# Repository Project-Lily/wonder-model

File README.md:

<div style="text-align: center">
<h1>Wonder Reader</h1>

<p>Repository for circuit, and 3D CAD models<p>
</div>

### Circuit

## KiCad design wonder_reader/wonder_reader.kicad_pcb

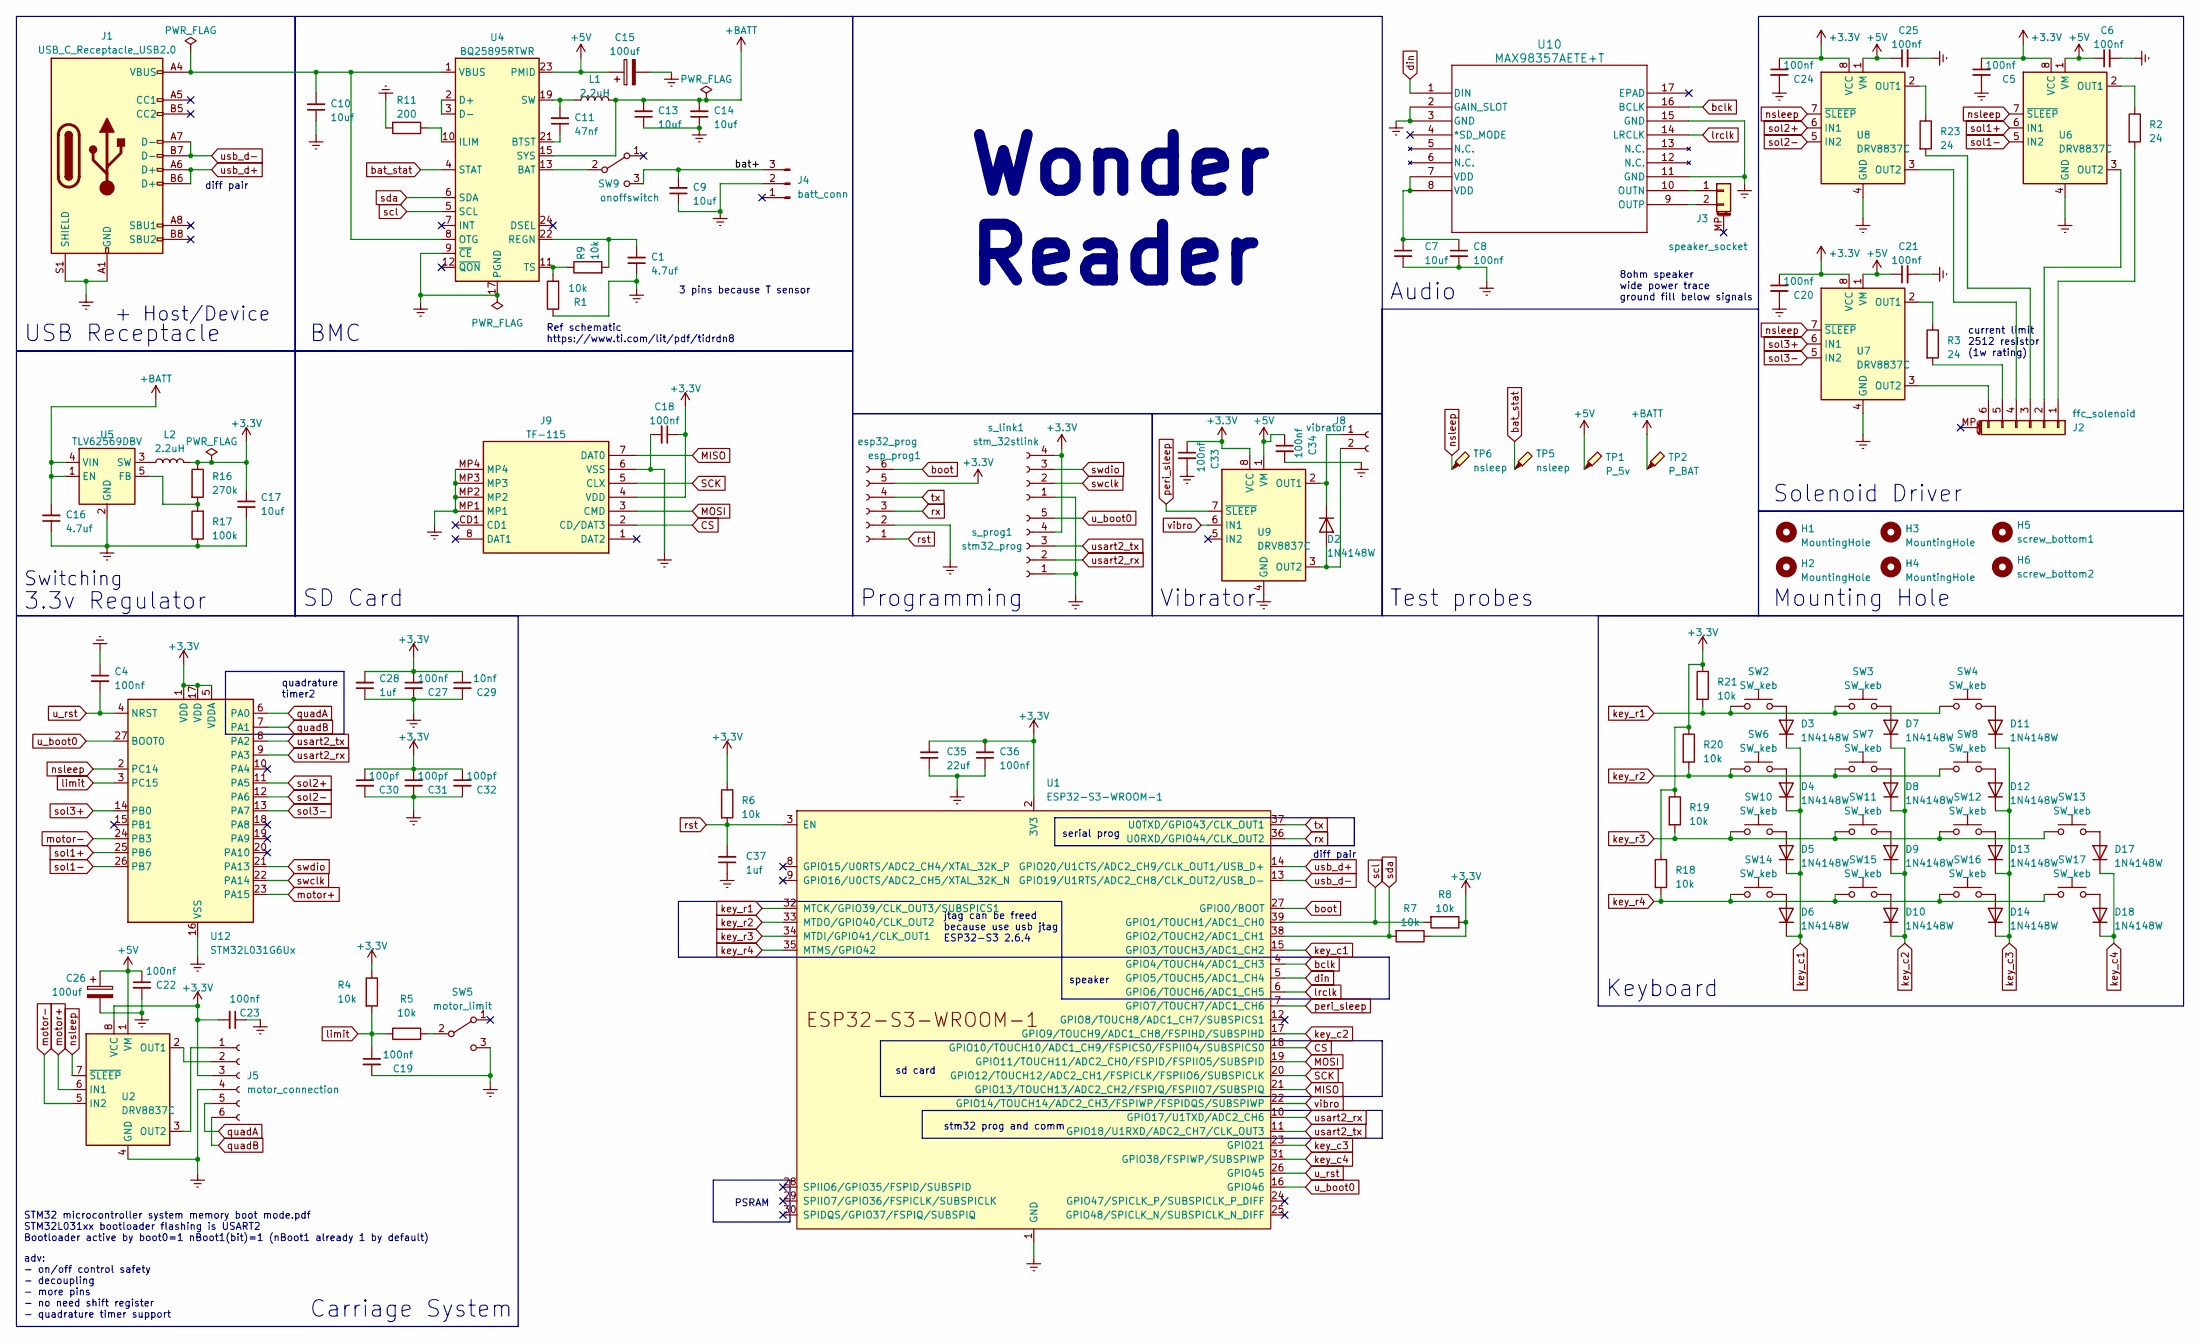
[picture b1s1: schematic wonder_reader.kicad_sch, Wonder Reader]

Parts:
C1, C16: 4.7uf; C_0805_2012Metric; LCSC Part C1779
C4, C5, C6, C8, C18, C19, C20, C21, C22, C23, C24, C25, C27, C33, C34, C36: 100nf; C_0402_1005Metric; LCSC Part C1525
C7, C9, C10, C13, C14, C17: 10uf; C_0805_2012Metric; LCSC Part C15850
C11: 47nf; C_0603_1608Metric; LCSC Part C1622
C15, C26: 100uf; CP_Elec_6.3x5.4; LCSC Part C1622
C28, C37: 1uf; C_0402_1005Metric; LCSC Part C52923
C29: 10nf; C_0402_1005Metric; LCSC Part C15195
C30, C31, C32: 100pf; C_0402_1005Metric; LCSC Part C1546
C35: 22uf; C_0805_2012Metric; LCSC Part C45783
D2, D3, D4, D5, D6, D7, D8, D9, D10, D11, D12, D13, D14, D17, D18: 1N4148W; D_SOD-123; LCSC Part C81598
H1, H2, H3, H4: MountingHole; MountingHole_2.2mm_M2
H5: screw_bottom1; MountingHole_5.3mm_M5
H6: screw_bottom2; MountingHole_5.3mm_M5
J1: USB_C_Receptacle_USB2.0; USB_C_Receptacle_G-Switch_GT-USB-7010ASV; LCSC Part C2765186
J2: ffc_solenoid; Hirose_FH12-6S-0.5SH_1x06-1MP_P0.50mm_Horizontal; LCSC Part C2856796
J3: speaker_socket; JST_GH_BM02B-GHS-TBT_1x02-1MP_P1.25mm_Vertical; LCSC Part C161690
J4: batt_conn; JST_PH_S3B-PH-K_1x03_P2.00mm_Horizontal; LCSC Part C157929
J5: motor_connection; PinHeader_1x06_P1.27mm_Vertical
J8: vibrator; PinHeader_1x02_P1.27mm_Vertical
J9: TF-115; TF115; Manufacturer_Part_Number TF-115; LCSC Part C266620
L1, L2: 2.2uH; L_1210_3225Metric; LCSC Part C295335
R1, R4, R5, R6, R7, R8, R9, R18, R19, R20, R21: 10k; R_0603_1608Metric; LCSC Part C25804
R2, R3, R23: 24; R_2512_6332Metric
R11: 200; R_0603_1608Metric; LCSC Part C8218
R16: 270k; R_0603_1608Metric; LCSC Part C103491
R17: 100k; R_0603_1608Metric; LCSC Part C25803
SW2, SW3, SW4, SW6, SW7, SW8, SW10, SW11, SW12, SW13, SW14, SW15, SW16, SW17: SW_keb; SW_Kailh_Choc_V1
SW5: motor_limit; SW_XKB_DM1-16UC-1; LCSC Part C466019
SW9: onoffswitch; G-Switch MK-12C02-G025; LCSC Part C963206
TP1: P_5v; TestPoint_Pad_1.0x1.0mm
TP2: P_BAT; TestPoint_Pad_1.0x1.0mm
TP5, TP6: nsleep; TestPoint_Pad_1.0x1.0mm
U1: ESP32-S3-WROOM-1; LCSC Part C2913197
U2, U6, U7, U8, U9: DRV8837C; WSON-8-1EP_2x2mm_P0.5mm_EP0.9x1.6mm; LCSC Part C191000
U4: BQ25895RTWR; Texas_S-PWQFN-N24_EP2.7x2.7mm_ThermalVias; LCSC Part C80200
U5: TLV62569DBV; SOT-23-5; LCSC Part C141836
U10: MAX98357AETE+T; 21-0136I_T1633-4_MXM; LCSC Part C910544
U12: STM32L031G6Ux; QFN-28_4x4mm_P0.5mm; LCSC Part C96514
esp_prog1: esp32_prog; PinHeader_1x06_P2.00mm_Vertical
s_link1: stm_32stlink; PinHeader_1x04_P2.00mm_Vertical
s_prog1: stm32_prog; PinHeader_1x05_P2.00mm_Vertical

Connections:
+3.3V: C5.1, C17.1, C18.1, C20.1, C23.2, C24.1, C27.1, C28.2, C29.1, C30.1, C31.1, C32.1, C33.1, C35.2, C36.2, J5.3, J9.4 (VDD), L2.2, R4.1, R6.1, R7.1, R8.1, R16.1, R18.1, R19.1, R20.1, R21.1, U1.2 (3V3), U2.8 (VCC), U6.8 (VCC), U7.8 (VCC), U8.8 (VCC), U9.8 (VCC), U12.1 (VDD), U12.5 (VDDA), U12.17 (VDD), esp_prog1.5, s_link1.4, s_prog1.4
+5V: C6.1, C15.1, C21.1, C22.1, C25.1, C26.1, C34.1, TP1.1, U2.1 (VM), U4.23 (PMID), U6.1 (VM), U7.1 (VM), U8.1 (VM), U9.1 (VM)
+BATT: C13.2, C14.2, C16.2, L1.2, TP2.1, U4.15 (SYS), U4.16 (SYS), U5.1 (EN), U5.4 (VIN)
/bat+: C9.2, J4.3, SW9.3 (C)
CS: J9.2 (CD/DAT3), U1.18 (GPIO10/TOUCH10/ADC1_CH9/FSPICS0/FSPIIO4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)
Earth: C1.1, C4.1, C5.2, C6.2, C7.2, C8.2, C9.1, C10.1, C13.1, C14.1, C15.2, C16.1, C17.2, C18.2, C19.2, C20.2, C21.2, C22.2, C23.1, C24.2, C25.2, C26.2, C27.2, C28.1, C29.2, C30.2, C31.2, C32.2, C33.2, C34.2, C35.1, C36.1, C37.1, J1.A1 (GND), J1.A12 (GND), J1.B1 (GND), J1.B12 (GND), J1.S1 (SHIELD), J4.2, J5.4, J9.6 (VSS), J9.MP1, J9.MP2, J9.MP3, J9.MP4, R1.1, R11.2, R17.1, SW5.3 (C), U1.1 (GND), U1.40 (GND), U1.41 (GND), U2.4 (GND), U2.9 (GND), U4.9 (~CE), U4.17 (PGND), U4.18 (PGND), U4.25 (PGND), U5.2 (GND), U6.4 (GND), U6.9 (GND), U7.4 (GND), U7.9 (GND), U8.4 (GND), U8.9 (GND), U9.4 (GND), U9.9 (GND), U10.2 (GAIN_SLOT), U10.3 (GND), U10.11 (GND), U10.15 (GND), U12.16 (VSS), U12.28 (VSS), esp_prog1.2, s_link1.1, s_prog1.1
MISO: J9.7 (DAT0), U1.21 (GPIO13/TOUCH13/ADC2_CH2/FSPIQ/FSPIIO7/S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)
MOSI: J9.3 (CMD), U1.19 (GPIO11/TOUCH11/ADC2_CH0/FSPID/FSPIIO5/S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)
unnamed: C7.1, C8.1, U10.7 (VDD), U10.8 (VDD)
unnamed: C11.2, L1.1, U4.19 (SW), U4.20 (SW)
unnamed: D2.2 (A), J8.2, U9.3 (OUT2)
unnamed: D2.1 (K), J8.1, U9.2 (OUT1)
unnamed: D3.2 (A), SW2.2
unnamed: D4.2 (A), SW6.2
unnamed: D5.2 (A), SW10.2
unnamed: D6.2 (A), SW14.2
unnamed: D7.2 (A), SW3.2
unnamed: D8.2 (A), SW7.2
unnamed: D9.2 (A), SW11.2
unnamed: D10.2 (A), SW15.2
unnamed: D11.2 (A), SW4.2
unnamed: D12.2 (A), SW8.2
unnamed: D13.2 (A), SW12.2
unnamed: D14.2 (A), SW16.2
unnamed: D17.2 (A), SW13.2
unnamed: D18.2 (A), SW17.2
unnamed: J2.1, R2.2
unnamed: J2.2, U6.3 (OUT2)
unnamed: J2.3, R23.2
unnamed: J2.4, U8.3 (OUT2)
unnamed: J2.5, R3.2
unnamed: J2.6, U7.3 (OUT2)
unnamed: J3.1, U10.10 (OUTN)
unnamed: J3.2, U10.9 (OUTP)
unnamed: J5.1, U2.3 (OUT2)
unnamed: J5.2, U2.2 (OUT1)
unnamed: R5.2, SW5.2 (B)
unnamed: SW9.2 (B), U4.13 (BAT), U4.14 (BAT)
unnamed: C11.1, U4.21 (BTST)
unnamed: U4.2 (D+), U4.3 (D-)
unnamed: R11.1, U4.10 (ILIM)
unnamed: C10.2, J1.A4 (VBUS), J1.A9 (VBUS), J1.B4 (VBUS), J1.B9 (VBUS), U4.1 (VBUS), U4.8 (OTG)
unnamed: C1.2, R9.2, U4.22 (REGN)
unnamed: R1.2, R9.1, U4.11 (TS)
unnamed: R16.2, R17.2, U5.5 (FB)
unnamed: L2.1, U5.3 (SW)
unnamed: R2.1, U6.2 (OUT1)
unnamed: R3.1, U7.2 (OUT1)
unnamed: R23.1, U8.2 (OUT1)
SCK: J9.5 (CLX), U1.20 (GPIO12/TOUCH12/ADC2_CH1/FSPICLK/FSPIIO6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)
bat_stat: TP5.1, U4.4 (STAT)
bclk: U1.4 (GPIO4/TOUCH4/ADC1_CH3), U10.16 (BCLK)
boot: U1.27 (GPIO0/BOOT), esp_prog1.6
din: U1.5 (GPIO5/TOUCH5/ADC1_CH4), U10.1 (DIN)
key_c1: D3.1 (K), D4.1 (K), D5.1 (K), D6.1 (K), U1.15 (GPIO3/TOUCH3/ADC1_CH2)
key_c2: D7.1 (K), D8.1 (K), D9.1 (K), D10.1 (K), U1.17 (GPIO9/TOUCH9/ADC1_CH8/FSPIHD/SUBSPIHD)
key_c3: D11.1 (K), D12.1 (K), D13.1 (K), D14.1 (K), U1.23 (GPIO21)
key_c4: D17.1 (K), D18.1 (K), U1.31 (GPIO38/FSPIWP/SUBSPIWP)
key_r1: R21.2, SW2.1, SW3.1, SW4.1, U1.32 (MTCK/GPIO39/CLK_OUT3/SUBSPICS1)
key_r2: R20.2, SW6.1, SW7.1, SW8.1, U1.33 (MTDO/GPIO40/CLK_OUT2)
key_r3: R19.2, SW10.1, SW11.1, SW12.1, SW13.1, U1.34 (MTDI/GPIO41/CLK_OUT1)
key_r4: R18.2, SW14.1, SW15.1, SW16.1, SW17.1, U1.35 (MTMS/GPIO42)
limit: C19.1, R4.2, R5.1, U12.3 (PC15)
lrclk: U1.6 (GPIO6/TOUCH6/ADC1_CH5), U10.14 (LRCLK)
motor+: U2.6 (IN1), U12.23 (PA15)
motor-: U2.5 (IN2), U12.24 (PB3)
nsleep: TP6.1, U2.7 (~SLEEP), U6.7 (~SLEEP), U7.7 (~SLEEP), U8.7 (~SLEEP), U12.2 (PC14)
peri_sleep: U1.7 (GPIO7/TOUCH7/ADC1_CH6), U9.7 (~SLEEP)
quadA: J5.5, U12.6 (PA0)
quadB: J5.6, U12.7 (PA1)
rst: C37.2, R6.2, U1.3 (EN), esp_prog1.1
rx: U1.36 (U0RXD/GPIO44/CLK_OUT2), esp_prog1.3
scl: R8.2, U1.39 (GPIO1/TOUCH1/ADC1_CH0), U4.5 (SCL)
sda: R7.2, U1.38 (GPIO2/TOUCH2/ADC1_CH1), U4.6 (SDA)
sol1+: U6.6 (IN1), U12.25 (PB6)
sol1-: U6.5 (IN2), U12.26 (PB7)
sol2+: U8.6 (IN1), U12.11 (PA5)
sol2-: U8.5 (IN2), U12.12 (PA6)
sol3+: U7.6 (IN1), U12.14 (PB0)
sol3-: U7.5 (IN2), U12.13 (PA7)
swclk: U12.22 (PA14), s_link1.2
swdio: U12.21 (PA13), s_link1.3
tx: U1.37 (U0TXD/GPIO43/CLK_OUT1), esp_prog1.4
u_boot0: U1.16 (GPIO46), U12.27 (BOOT0), s_prog1.5
u_rst: C4.2, U1.26 (GPIO45), U12.4 (NRST)
usart2_rx: U1.10 (GPIO17/U1TXD/ADC2_CH6), U12.9 (PA3), s_prog1.2
usart2_tx: U1.11 (GPIO18/U1RXD/ADC2_CH7/CLK_OUT3), U12.8 (PA2), s_prog1.3
usb_d+: J1.A6 (D+), J1.B6 (D+), U1.14 (GPIO20/U1CTS/ADC2_CH9/CLK_OUT1/USB_D+)
usb_d-: J1.A7 (D-), J1.B7 (D-), U1.13 (GPIO19/U1RTS/ADC2_CH8/CLK_OUT2/USB_D-)
vibro: U1.22 (GPIO14/TOUCH14/ADC2_CH3/FSPIWP/FSPIDQS/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), U9.6 (IN1)

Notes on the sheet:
BMC
3 pins because T sensor
8ohm speaker wide power trace ground fill below signals
Wonder Reader
STM32 microcontroller system memory boot mode.pdf STM32L031xx bootloader flashing is USART2 Bootloader active by boot0=1 nBoot1(bit)=1 (nBoot1 already 1 by default)
Mounting Hole
USB Receptacle
sd card
Ref schematic https://www.ti.com/lit/pdf/tidrdn8
Solenoid Driver
diff pair
+ Host/Device
quadrature timer2
3.3v Regulator
stm32 prog and comm
Vibrator
Keyboard
speaker
current limit 2512 resistor (1w rating)
jtag can be freed because use usb jtag ESP32-S3 2.6.4
Programming
Test probes
SD Card
Audio
serial prog
adv: - on/off control safety - decoupling - more pins - no need shift register - quadrature timer support
Switching
Carriage System
PSRAM

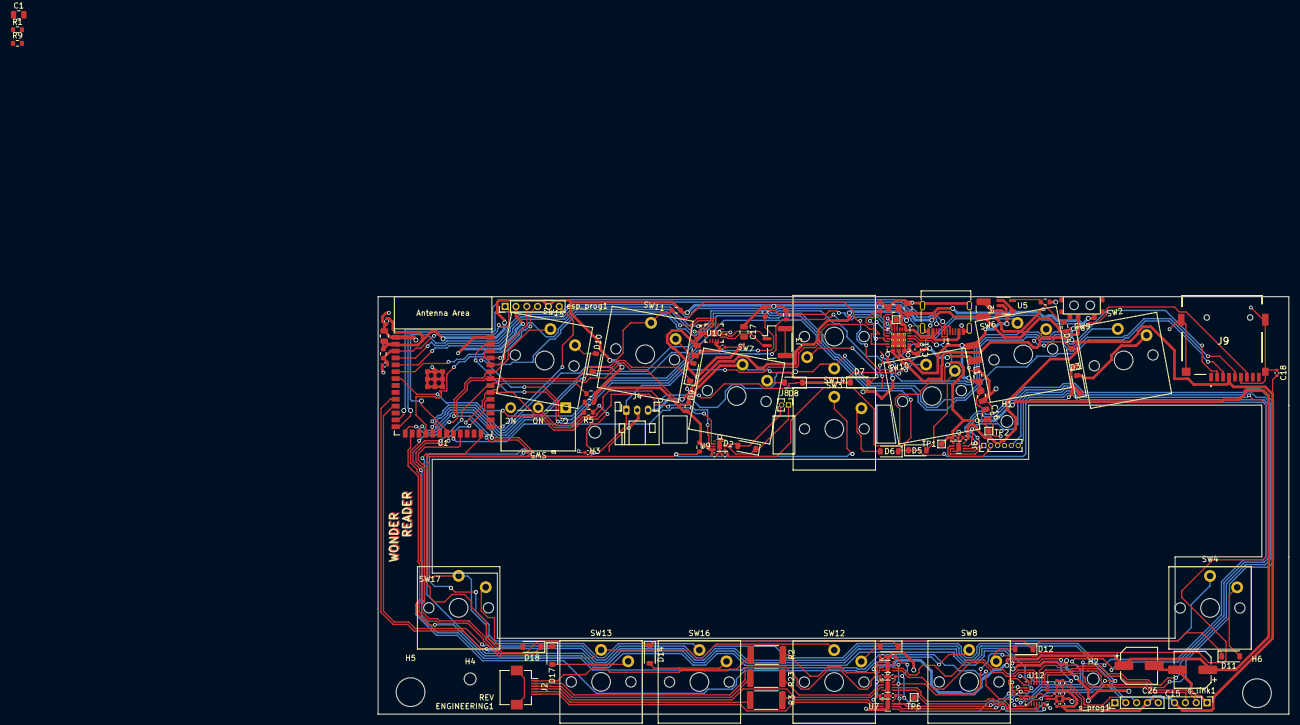
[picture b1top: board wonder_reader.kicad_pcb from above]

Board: 2 copper layers, 168.0 x 77.0 mm, 114 parts (0 on the bottom side), 90 nets.

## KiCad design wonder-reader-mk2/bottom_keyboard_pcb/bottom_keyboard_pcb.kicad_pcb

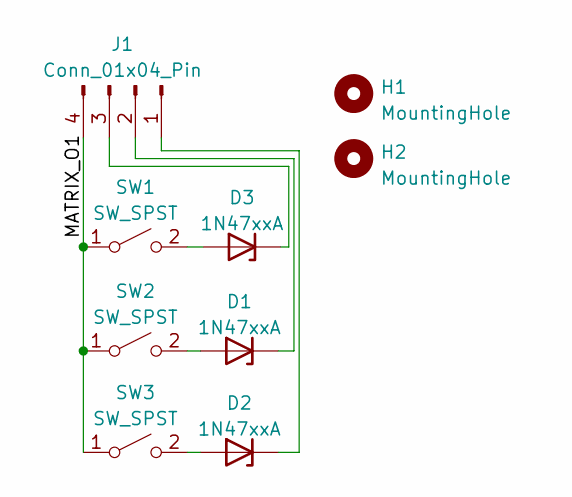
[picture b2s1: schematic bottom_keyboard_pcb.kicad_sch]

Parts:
D1, D2, D3: 1N47xxA; D_DO-41_SOD81_P5.08mm_Vertical_AnodeUp
H1, H2: MountingHole; MountingHole_3.2mm_M3
J1: Conn_01x04_Pin; PinHeader_1x04_P2.54mm_Vertical
SW1, SW2, SW3: SW_SPST; SW_Kailh_Choc_V1

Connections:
/MATRIX_O1: J1.4, SW1.1 (A), SW2.1 (A), SW3.1 (A)
unnamed: D1.2 (A), SW2.2 (B)
unnamed: D1.1 (K), J1.2
unnamed: D2.2 (A), SW3.2 (B)
unnamed: D2.1 (K), J1.1
unnamed: D3.2 (A), SW1.2 (B)
unnamed: D3.1 (K), J1.3

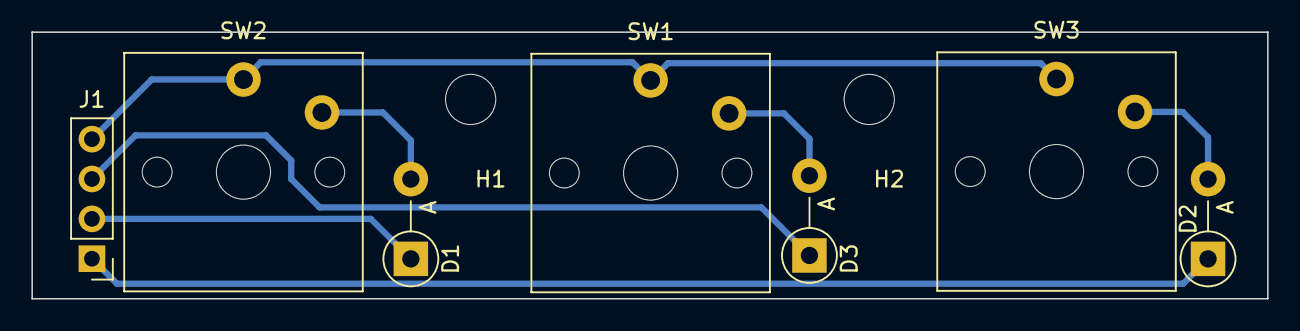
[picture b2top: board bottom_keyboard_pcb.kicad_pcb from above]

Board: 2 copper layers, 78.7 x 17.0 mm, 9 parts (0 on the bottom side), 7 nets.

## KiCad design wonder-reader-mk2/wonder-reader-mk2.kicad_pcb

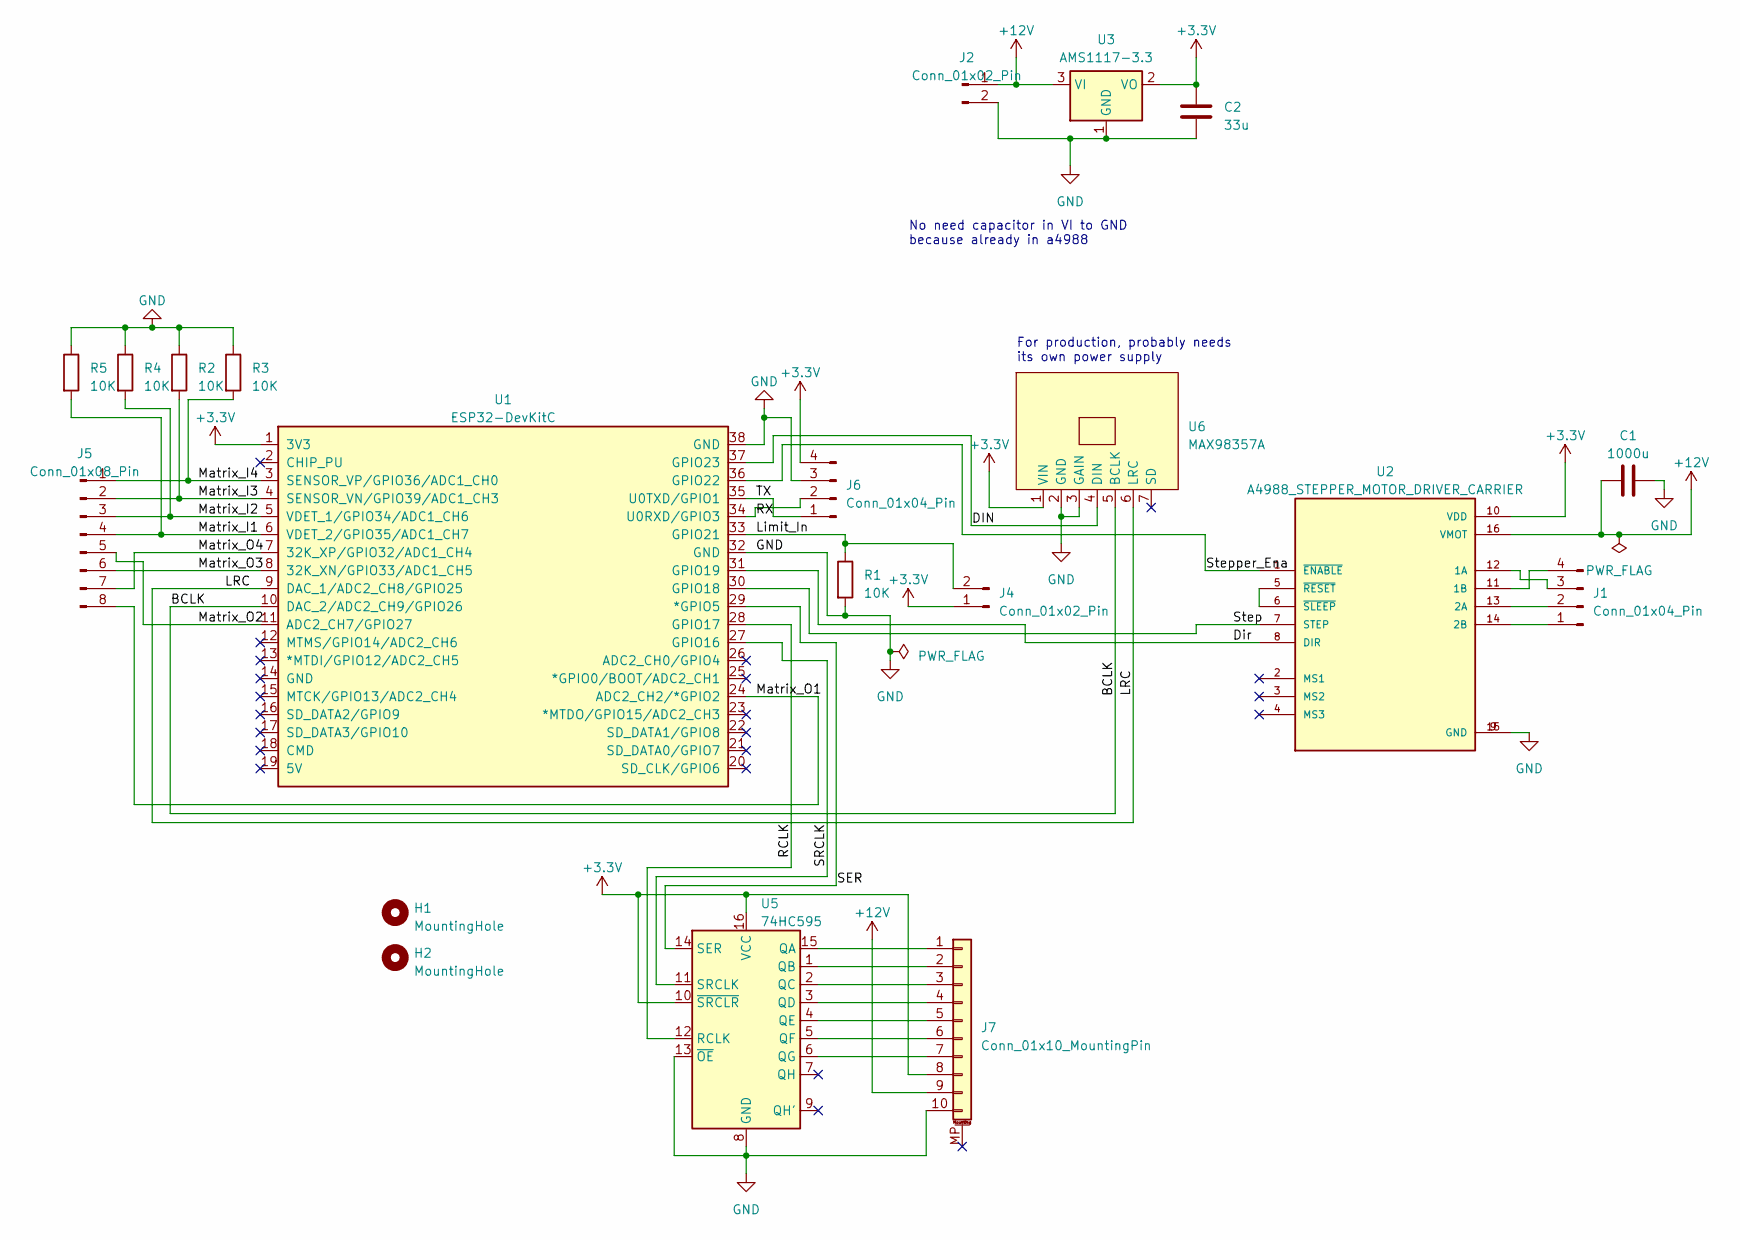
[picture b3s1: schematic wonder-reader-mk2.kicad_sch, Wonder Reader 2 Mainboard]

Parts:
C1: 1000u; C_Radial_D10.0mm_H16.0mm_P5.00mm
C2: 33u; C_Radial_D5.0mm_H11.0mm_P2.00mm
H1, H2: MountingHole; MountingHole_2.2mm_M2
J1: Conn_01x04_Pin; PinSocket_1x04_P2.54mm_Vertical
J2, J4: Conn_01x02_Pin; PinHeader_1x02_P2.54mm_Vertical
J5: Conn_01x08_Pin; PinHeader_1x08_P2.54mm_Vertical
J6: Conn_01x04_Pin; PinHeader_1x04_P2.54mm_Vertical
J7: Conn_01x10_MountingPin; Hirose_FH12-10S-0.5SH_1x10-1MP_P0.50mm_Horizontal
R1, R2, R3, R4, R5: 10K; R_0805_2012Metric
U1: ESP32-DevKitC
U2: A4988_STEPPER_MOTOR_DRIVER_CARRIER; MODULE_A4988_STEPPER_MOTOR_DRIVER_CARRIER
U3: AMS1117-3.3; SOT-223-3_TabPin2
U5: 74HC595; DIP-16_W7.62mm
U6: MAX98357A

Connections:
+3.3V: C2.2, J4.1, J6.4, J7.8, U1.1 (3V3), U2.10 (VDD), U3.2 (VO), U5.10 (~SRCLR), U5.16 (VCC), U6.1 (VIN)
+12V: C1.1, J2.1, J7.9, U2.16 (VMOT), U3.3 (VI)
/BCLK: U1.10 (DAC_2/ADC2_CH9/GPIO26), U6.5 (BCLK)
/DIN: U1.37 (GPIO23), U6.4 (DIN)
/Dir: U1.31 (GPIO19), U2.8 (DIR)
/LRC: U1.9 (DAC_1/ADC2_CH8/GPIO25), U6.6 (LRC)
/Limit_In: J4.2, R1.1, U1.33 (GPIO21)
/Matrix_I1: J5.4, R5.2, U1.6 (VDET_2/GPIO35/ADC1_CH7)
/Matrix_I2: J5.3, R4.2, U1.5 (VDET_1/GPIO34/ADC1_CH6)
/Matrix_I3: J5.2, R2.2, U1.4 (SENSOR_VN/GPIO39/ADC1_CH3)
/Matrix_I4: J5.1, R3.2, U1.3 (SENSOR_VP/GPIO36/ADC1_CH0)
/Matrix_O1: J5.8, U1.24 (ADC2_CH2/*GPIO2)
/Matrix_O2: J5.5, U1.11 (ADC2_CH7/GPIO27)
/Matrix_O3: J5.6, U1.8 (32K_XN/GPIO33/ADC1_CH5)
/Matrix_O4: J5.7, U1.7 (32K_XP/GPIO32/ADC1_CH4)
/RCLK: U1.28 (GPIO17), U5.12 (RCLK)
/RX: J6.2, U1.34 (U0RXD/GPIO3)
/SER: U1.29 (*GPIO5), U5.14 (SER)
/SRCLK: U1.27 (GPIO16), U5.11 (SRCLK)
/Step: U1.30 (GPIO18), U2.7 (STEP)
/Stepper_Ena: U1.36 (GPIO22), U2.1 (~ENABLE)
/TX: J6.1, U1.35 (U0TXD/GPIO1)
GND: C1.2, C2.1, J2.2, J6.3, J7.10, R1.2, R2.1, R3.1, R4.1, R5.1, U1.32 (GND), U1.38 (GND), U2.9 (GND), U2.15 (GND), U3.1 (GND), U5.8 (GND), U5.13 (~OE), U6.2 (GND), U6.3 (GAIN)
unnamed: J1.1, U2.14 (2B)
unnamed: J1.2, U2.13 (2A)
unnamed: J1.3, U2.12 (1A)
unnamed: J1.4, U2.11 (1B)
unnamed: J7.1, U5.15 (QA)
unnamed: J7.2, U5.1 (QB)
unnamed: J7.3, U5.2 (QC)
unnamed: J7.4, U5.3 (QD)
unnamed: J7.5, U5.4 (QE)
unnamed: J7.6, U5.5 (QF)
unnamed: J7.7, U5.6 (QG)
unnamed: U2.5 (~RESET), U2.6 (~SLEEP)

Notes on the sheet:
No need capacitor in VI to GND because already in a4988
For production, probably needs its own power supply

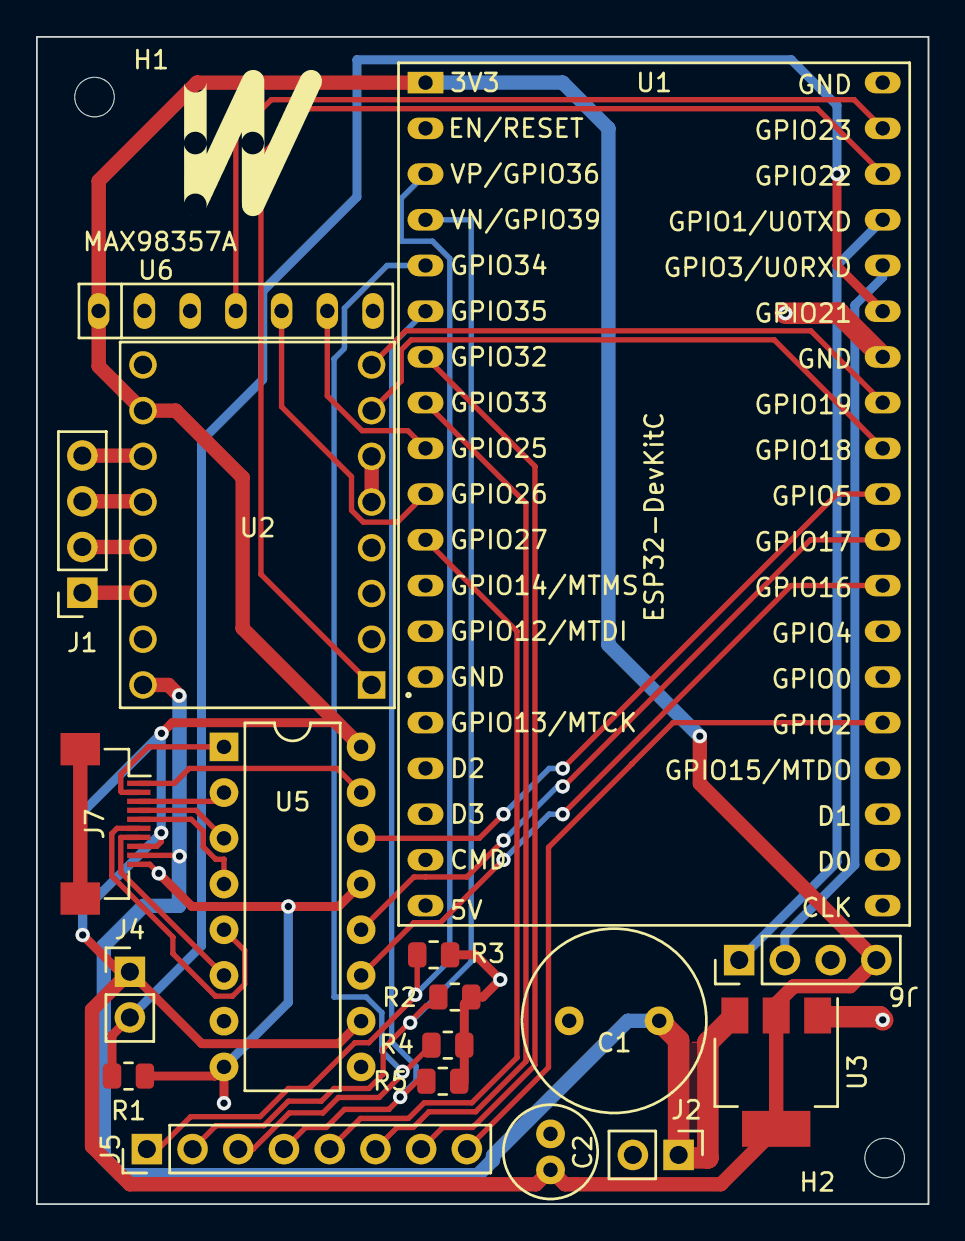
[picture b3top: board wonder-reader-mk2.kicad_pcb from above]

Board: 2 copper layers, 49.5 x 64.8 mm, 20 parts (0 on the bottom side), 35 nets.

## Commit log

2023-01-26 First prototype
2023-02-05 Added wonder reader mk1 files
2023-02-05 Initial design for mk2
2023-02-10 Added some carriage components
2023-02-15 Added updated cad models to hopefully final cell design. Added some renders
2023-02-20 Added kicad schematic design
2023-02-28 Updated cell top height. Carriage load now can be joined together as they have a connecttor. New gearbox for x stepper motor speed. Updated PCB design
2023-03-06 New 1:3 gearbox. Bearing bracket start second gear holder not hitting screw
2023-03-09 Added new model for new carriage
2023-04-02 Added cases and switches. Updated carriage load models and bearing brackets. Schematic update
2023-04-02 Added epic pictures
2023-05-15 Added new pcb and more step files for mark 2. Renamed previous mark 2 to mark 1 and mark 1 to mark 0
2023-06-01 PCB and new models for mark 2
2023-06-03 Updated arm and wedge model for more stability
2023-06-04 Updated readme md images cool
2023-12-19 Added new Wonder Reader schematics
2024-01-09 Completed new wonder reader pcb
2024-01-10 Updated pcb to lower costs and rectify faults
